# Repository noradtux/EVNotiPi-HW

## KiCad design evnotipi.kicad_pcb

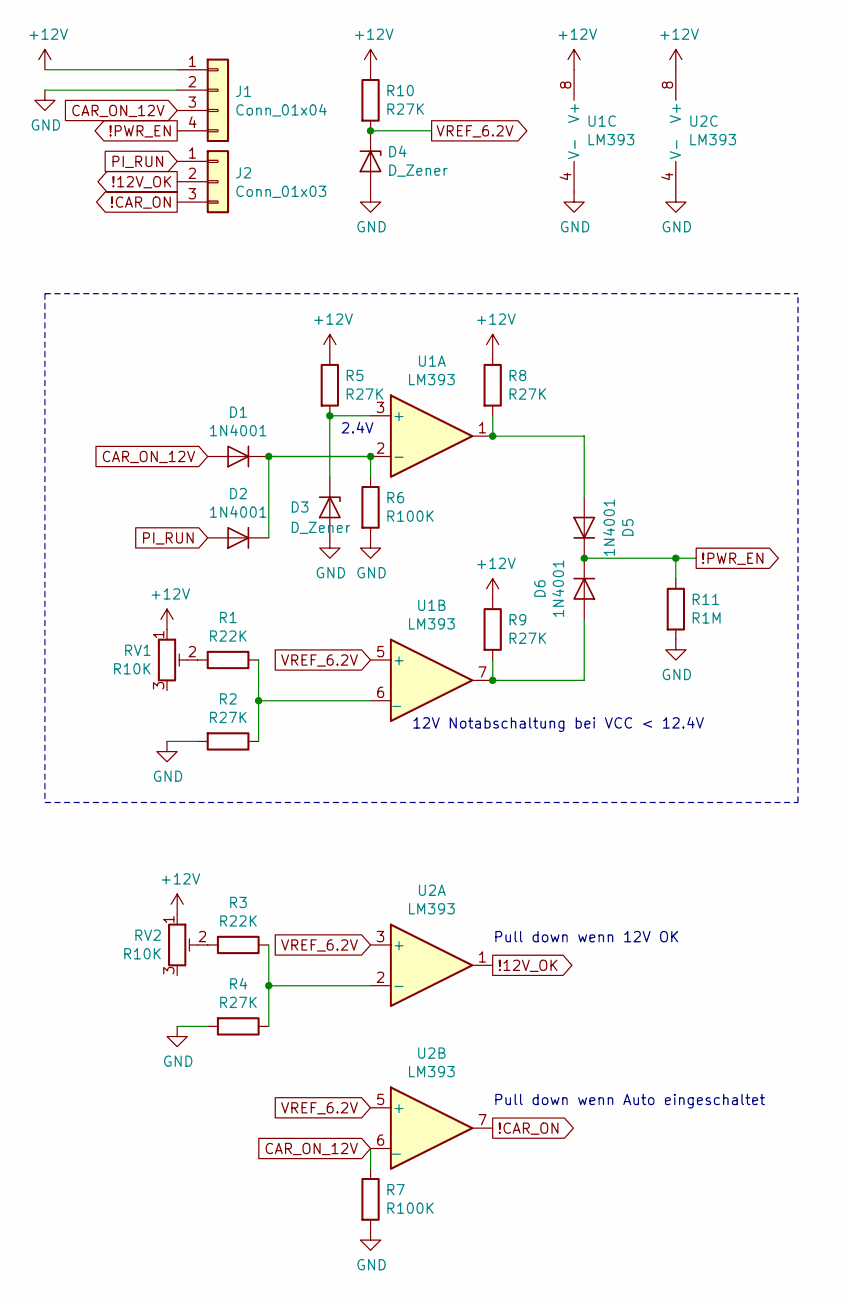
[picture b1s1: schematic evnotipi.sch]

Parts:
D1, D2, D5, D6: 1N4001; D_DO-41_SOD81_P10.16mm_Horizontal
D3, D4: D_Zener; D_DO-35_SOD27_P7.62mm_Horizontal
J1: Conn_01x04; PinHeader_1x04_P2.54mm_Horizontal
J2: Conn_01x03; PinHeader_1x03_P2.54mm_Horizontal
R1, R3: R22K; R_Axial_DIN0207_L6.3mm_D2.5mm_P7.62mm_Horizontal
R2, R4, R5, R8, R9, R10: R27K; R_Axial_DIN0207_L6.3mm_D2.5mm_P7.62mm_Horizontal
R6, R7: R100K; R_Axial_DIN0207_L6.3mm_D2.5mm_P7.62mm_Horizontal
R11: R1M; R_Axial_DIN0207_L6.3mm_D2.5mm_P7.62mm_Horizontal
RV1, RV2: R10K; Potentiometer_Bourns_3296Y_Vertical
U1, U2: LM393; DIP-8_W7.62mm_Socket

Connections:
!12V_OK: J2.2, U2.1
!CAR_ON: J2.3, U2.7
!PWR_EN: D5.1 (K), D6.1 (K), J1.4, R11.1
+12V: J1.1, R5.1, R8.1, R9.1, R10.1, RV1.1, RV2.1, U1.8 (V+), U2.8 (V+)
CAR_ON_12V: D1.2 (A), J1.3, R7.1, U2.6 (_)
GND: D3.2 (A), D4.2 (A), J1.2, R2.2, R4.2, R6.2, R7.2, R11.2, U1.4 (V-), U2.4 (V-)
unnamed: D1.1 (K), D2.1 (K), R6.1, U1.2 (-)
unnamed: D3.1 (K), R5.2, U1.3 (+)
unnamed: D5.2 (A), R8.2, U1.1
unnamed: D6.2 (A), R9.2, U1.7
unnamed: R1.1, R2.1, U1.6 (_)
unnamed: R1.2, RV1.2
unnamed: R3.1, R4.1, U2.2 (-)
unnamed: R3.2, RV2.2
PI_RUN: D2.2 (A), J2.1
VREF_6.2V: D4.1 (K), R10.2, U1.5 (+), U2.3 (+), U2.5 (+)

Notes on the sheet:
2.4V
12V Notabschaltung bei VCC < 12.4V
Pull down wenn 12V OK
Pull down wenn Auto eingeschaltet

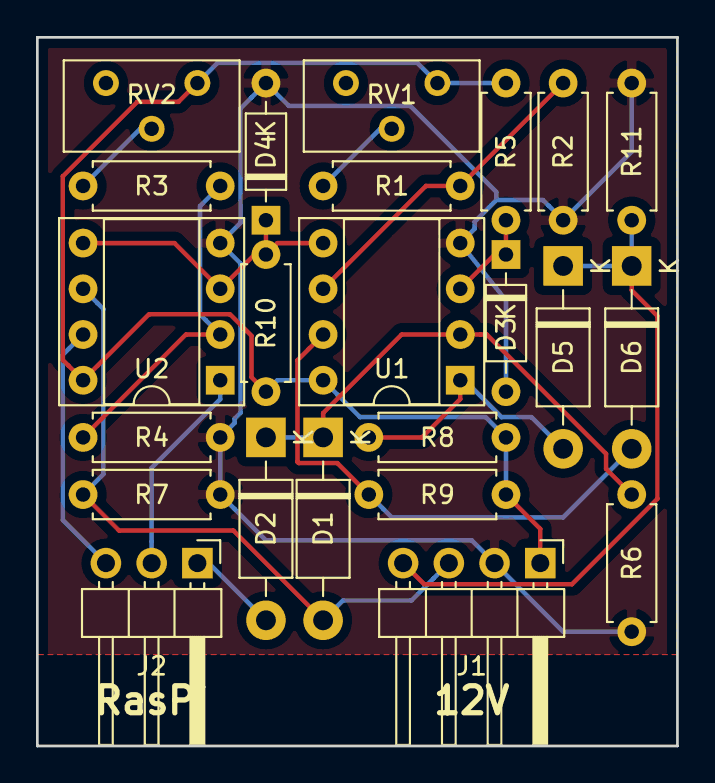
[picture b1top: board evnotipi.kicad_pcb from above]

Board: 2 copper layers, 35.6 x 39.4 mm, 23 parts (0 on the bottom side), 16 nets.

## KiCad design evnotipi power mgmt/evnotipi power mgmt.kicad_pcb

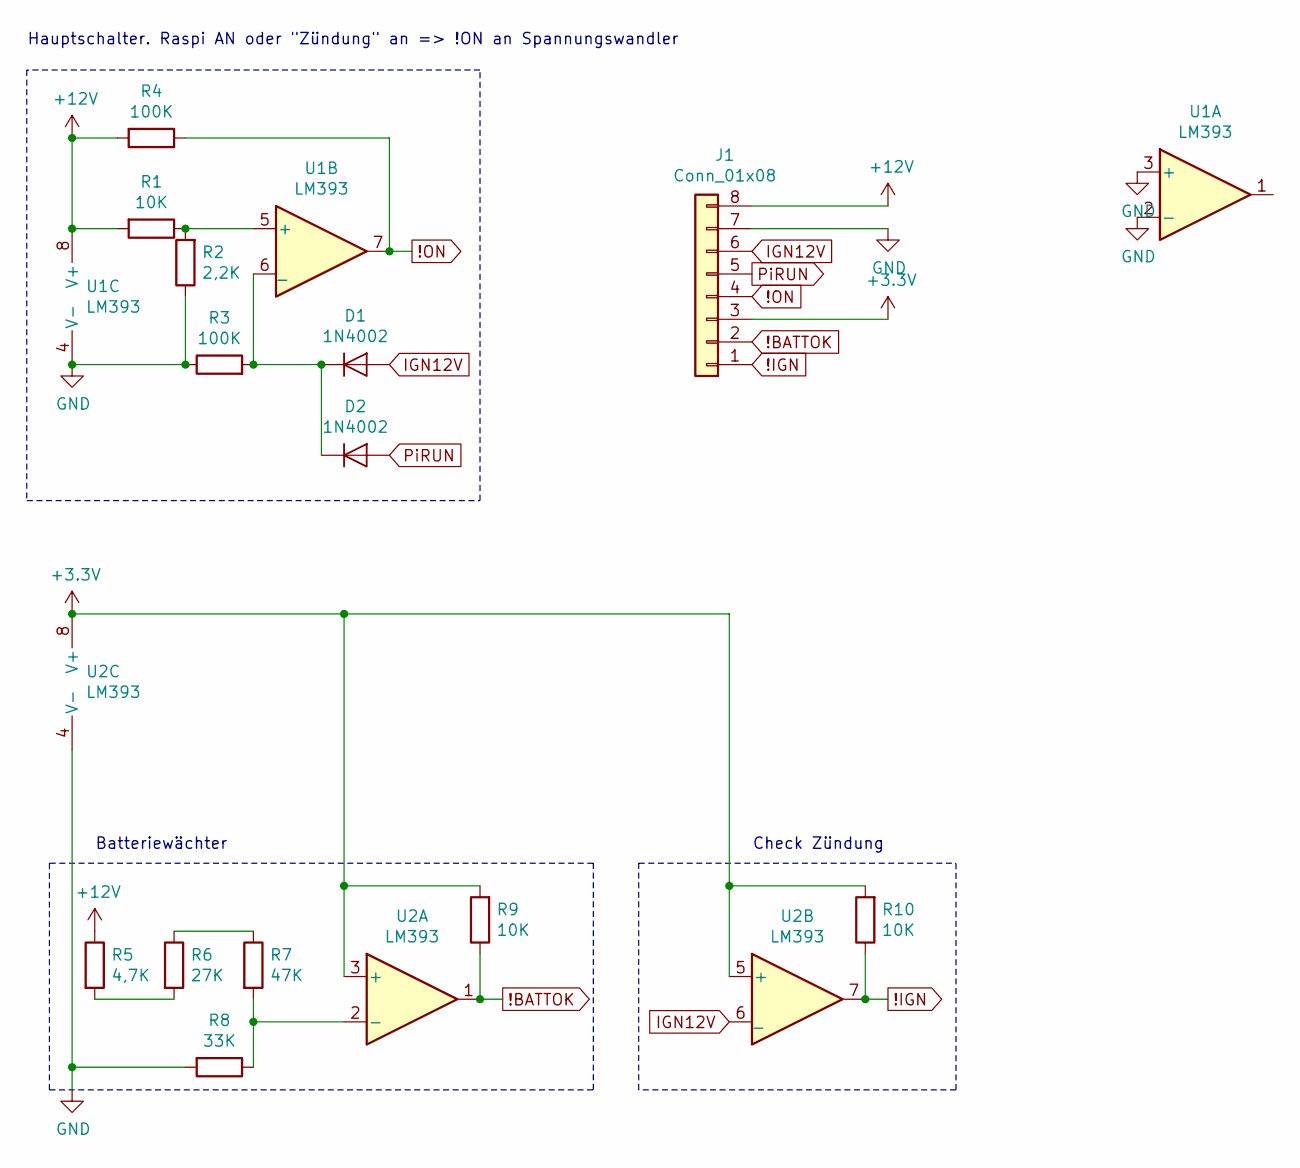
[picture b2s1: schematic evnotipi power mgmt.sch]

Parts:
D1, D2: 1N4002; D_DO-41_SOD81_P10.16mm_Horizontal
J1: Conn_01x08; PinHeader_1x08_P2.54mm_Horizontal
R1, R9, R10: 10K; R_Axial_DIN0207_L6.3mm_D2.5mm_P7.62mm_Horizontal
R2: 2,2K; R_Axial_DIN0207_L6.3mm_D2.5mm_P7.62mm_Horizontal
R3, R4: 100K; R_Axial_DIN0207_L6.3mm_D2.5mm_P7.62mm_Horizontal
R5: 4,7K; R_Axial_DIN0207_L6.3mm_D2.5mm_P7.62mm_Horizontal
R6: 27K; R_Axial_DIN0207_L6.3mm_D2.5mm_P7.62mm_Horizontal
R7: 47K; R_Axial_DIN0207_L6.3mm_D2.5mm_P7.62mm_Horizontal
R8: 33K; R_Axial_DIN0207_L6.3mm_D2.5mm_P7.62mm_Horizontal
U1, U2: LM393; DIP-8_W7.62mm

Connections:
!BATTOK: J1.2, R9.1, U2.1
!IGN: J1.1, R10.1, U2.7
!ON: J1.4, R4.1, U1.7
+3V3: J1.3, R9.2, R10.2, U2.3 (+), U2.5 (+), U2.8 (V+)
+12V: J1.8, R1.2, R4.2, R5.1, U1.8 (V+)
GND: J1.7, R2.1, R3.1, R8.2, U1.2 (-), U1.3 (+), U1.4 (V-), U2.4 (V-)
IGN12V: D1.2 (A), J1.6, U2.6 (_)
unnamed: D1.1 (K), D2.1 (K), R3.2, U1.6 (_)
unnamed: R1.1, R2.2, U1.5 (+)
unnamed: R5.2, R6.2
unnamed: R6.1, R7.1
unnamed: R7.2, R8.1, U2.2 (-)
PiRUN: D2.2 (A), J1.5

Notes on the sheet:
Hauptschalter. Raspi AN oder "Zündung" an => !ON an Spannungswandler
Check Zündung
Batteriewächter

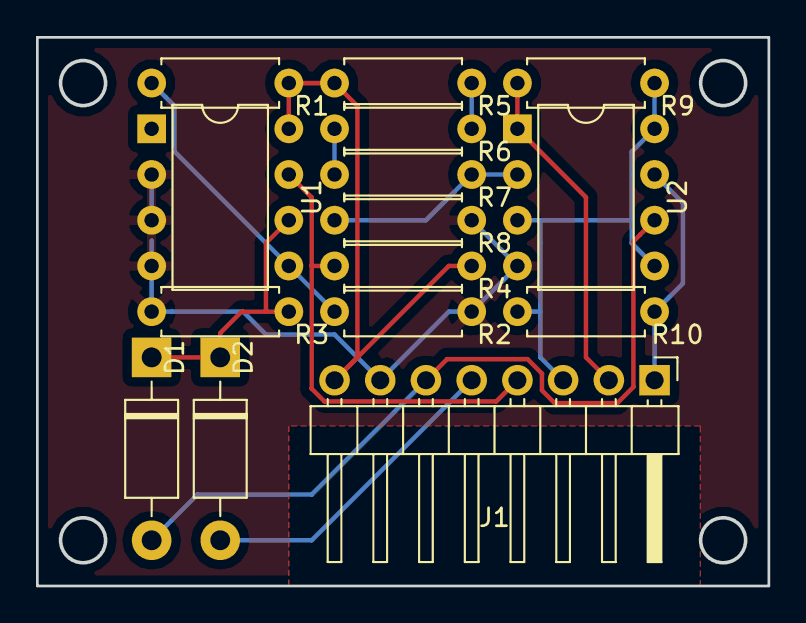
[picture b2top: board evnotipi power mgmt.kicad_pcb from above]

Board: 2 copper layers, 40.6 x 30.4 mm, 15 parts (0 on the bottom side), 13 nets.

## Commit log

2019-03-31 final version
2019-04-09 Fine adjust voltage splitter
